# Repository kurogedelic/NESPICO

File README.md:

# NESPICO

A low-cost USB Famicom cartridge reader and **live-cartridge console** experiment.

The cartridge is not just a source for a ROM dump: the eventual console should drive the inserted physical cartridge's CPU and PPU buses while running the NES CPU/PPU/APU on an RP2350. The host PC or Mac handles display, audio playback, and controls.

## Project overview

```text
Physical Famicom 60-pin cartridge
               |
     74-series bus interface
     (latches / transceivers)
               |
      Raspberry Pi Pico 2 + PIO
               |
           USB Full Speed
               |
           PC / Mac host
   video, audio, controls, dumps
```

**Target hardware:** standard non-wireless Raspberry Pi Pico 2 (RP2350), 74-series logic, a real 60-pin cartridge connector and USB. The Pico 2 exposes 26 header GPIOs (GP0–GP22, GP26–GP28). For this design, GP26–GP28 are reserved for ADC0–ADC2 analog inputs; GP29 is ADC3 used by the board's VSYS monitor and is not a header GPIO. This leaves **23 digital GPIOs (GP0–GP22)**, so the earlier 27-GPIO concept must move at least four functions into external logic or be redesigned. No FPGA, HDMI shield or wireless module is planned. GPIO allocation and electrical protection are not finalized; see the [board architecture proposal](hardware/kicad/board-plan.md).

## Goals

1. **Play real cartridges.** Read PRG and CHR from the inserted cartridge during execution, support cartridge-side bank switching, CHR-RAM and mapper-generated IRQs instead of silently substituting a fully dumped ROM.
2. **Dump cartridges.** Read PRG-ROM and CHR-ROM to a host computer over USB, verify dumps, and support applicable mapper-controlled banks and cartridge save RAM.
3. **Reproduce physical-console behavior.** Keep motherboard RAM across RESET and cartridge replacement with power retained. Test tricks such as **Tennis → Super Mario Bros. World 9**. This is **not** a request for automatic hot-swap detection or live game switching; cartridge removal with power applied also needs electrical safety validation.
4. **Use the computer as the display.** Stream enough video/audio information over USB for a small PC/Mac viewer, and receive controller input from the host. USB Full Speed means raw full-frame 60fps video is not a feasible default protocol.
5. **Keep the hardware inexpensive and buildable in a quantity of two.** Prefer off-the-shelf Pico 2 boards, inexpensive standard logic and hand-assembled connectors to a custom MCU/FPGA board.

## Development approach

**Simulation first, hardware second.** The host-side simulator models approximate NTSC CPU/PPU bus demand, nominal 74-series/PIO transaction latency, overlapping requests, simplified MMC3 A12 qualification, RESET RAM retention and USB bandwidth assumptions. GitHub Actions runs the tests without any connected hardware.

The simulation is a *screening tool*, not proof that physical timing works. It does not execute actual PIO, emulate a complete 6502/PPU, validate the cartridge voltage interface, or establish real USB throughput. PPU events use classified 2-dot fetch slots from the documented rendering schedule, but do not include generated PPU addresses or rendering-state changes.

### Current status

- Host-side deterministic bus-timing simulator and 39 regression tests are present, including exhaustive five-step checks of the abstract shared-bus guard and PPU fetch-slot phase checks. The local suite and Pico SDK 2.3.1 firmware builds pass; invalid test GPIO maps are rejected before compilation. Both GitHub Actions workflows passed for commit `8f26041` on `work/rp2350-pio-bringup`.
- Firmware CI checks PIO instruction order, sample strobe side-set, loop width, and agreement between the calculated 99 instruction clocks and C constants. It builds a second test map using Pico 2 header GPIOs GP20–GP22 and GP26–GP28, and rejects duplicate, malformed, out-of-range, leading-zero, and board-reserved GPIO assignments. These are source/configuration checks, not hardware execution.
- A one-bit AHCT/LVC level-interface candidate schematic and a 35-case switch-level SPICE screen are now available under `hardware/`; the assumed cartridge release timing is not measured, so this is not electrical sign-off.
- GPIO pin map, 5V interface, physical timing, accurate NES emulator, cartridge swapping and USB video protocol remain to be validated.
- **No claim of working cartridge playback or real-device ROM dumping yet.**

### Local checks

```sh
python -m unittest discover -s tests -v
python -m nespico.cli --scanlines 262
python -m nespico.cli --sys-mhz 20 --settle-ns 160 --scanlines 1 # expected failure
python3 firmware/pio_bringup/validate_pio_source.py
```

## Development records

- [Development log (2026-10-12)](docs/journal/2026-10-12.md)
- [Development roadmap](docs/roadmap.md)
- [Simulation results](docs/benchmark-results.md)
- [PIO bring-up checkpoint](docs/pio-bringup.md)
- [Preliminary one-bit KiCad interface slice](hardware/kicad/README.md) and [Pico 2 board architecture proposal](hardware/kicad/board-plan.md)
- [Bus-turnaround SPICE screening model](hardware/spice/README.md)

## Milestones

1. CI timing simulator + executable design assumptions
2. PIO bus-pattern generator on Pico 2, measured with loopback and a logic analyzer
3. 74-series interface prototype: safe NROM PRG/CHR readback
4. USB dumper with validation and mapper-aware read/write
5. Real-cart CPU+PPU operation, host video/audio and input
6. RAM-preserving RESET, cartridge replacement tests and MMC1/MMC3

See [architecture notes](docs/architecture.md) and [simulation results](docs/benchmark-results.md). The extra pipeline tests model the CPU/PPU work required to prepare addresses; they show that nominal bus-only timing success is not sufficient.

The first Pico SDK / PIO firmware target is a **test-only dual-lane GPIO loopback** under `firmware/pio_bringup/`. It is intentionally not a cartridge bus driver; see its [build and safety instructions](firmware/pio_bringup/README.md). A board-specific pinout and real logic-analyzer measurements are still required before freezing a cartridge interface or releasing PCB files for fabrication.

Reference documentation: [NESdev cartridge connector](https://www.nesdev.org/wiki/Cartridge_connector), [PPU rendering](https://www.nesdev.org/wiki/PPU_rendering), [MMC3](https://www.nesdev.org/wiki/MMC3), [RP2350](https://www.raspberrypi.com/documentation/microcontrollers/silicon.html).

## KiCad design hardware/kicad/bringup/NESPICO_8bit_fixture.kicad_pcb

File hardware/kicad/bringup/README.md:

# NESPICO Pico 2 8-bit bring-up fixture (draft)

This is a **bench-test fixture**, not the full Famicom cartridge interface and **not a fabrication release**. It exercises two independent 8-bit paths around a standard, non-wireless Raspberry Pi Pico 2:

- **CPU TX:** Pico GP0–GP7 → SN74AHCT245 (A→B, 5 V side) → J3 test header.
- **PPU RX:** J4 5 V-tolerant test header → SN74LVC245A (B→A) → Pico GP8–GP15.
- **Controls:** GP16 drives TX_OE_N; GP17 drives RX_OE_N. Separate 10 kΩ pull-ups keep both active-low enables disabled while the Pico is high impedance.
- **ADC breakout:** GP26–GP28 are analog-only. GP29 is not routed; the Pico 2 uses it internally for VSYS/3 measurement.
- **Power boundary:** USB VBUS powers only the AHCT test buffer. No cartridge power rail or cartridge connector is present. J3/J4 are labelled test-only.

The current rectangular outline is 100 × 82 mm, with two copper layers. The Pico 2 socket rows are 17.78 mm apart and span 48.26 mm. J1/J2 are standard 1×20 socket-strip footprints; confirm the actual socket height and module fit before assembly.

## Pico 2 physical-pin mapping

The local 1×20 connector pad number follows the footprint from top to bottom. With the Pico USB connector at the top, the left side is physical pins 1→20 (`J1`), while the right side is physical pins 40→21 (`J2`). This orientation is checked against Figure 4 of the [Raspberry Pi Pico 2 datasheet](https://pip.raspberrypi.com/documents/RP-008299-DS).

| PCB connector/pad | Pico 2 physical pin | Pico signal | Fixture net / destination |
| --- | ---: | --- | --- |
| J2.1 | 40 | VBUS | +5V_USB, U1 only |
| J2.5 | 36 | 3V3 | +3V3 logic rail |
| J2.7 | 34 | GP28 / ADC2 | J5.1, ADC2_IN |
| J2.8 | 33 | AGND | J5.2, AGND |
| J2.9 | 32 | GP27 / ADC1 | J5.3, ADC1_IN |
| J2.10 | 31 | GP26 / ADC0 | J5.4, ADC0_IN |
| J2.19 | 22 | GP17 | RX_OE_N |
| J2.20 | 21 | GP16 | TX_OE_N |

**J5 order:** `1 ADC2`, `2 AGND`, `3 ADC1`, `4 ADC0`. Keep GP26–GP28 exclusively for analog use in this pin-allocation baseline. **Never drive J5 above 3.3 V or while the Pico is unpowered.** There is no input divider, series protection, or source-conditioning network because the analog source has not been defined; only connect a reviewed 0–3.3 V source with suitable impedance. GP29/ADC3 is internal to the Pico 2 and is not broken out.

## Candidate parts (not a qualified production BOM)

| Reference | Candidate | Footprint | Notes |
| --- | --- | --- | --- |
| U1 | SN74AHCT245DW | SOIC-20W | 5 V supply; fixed A→B; 3.3 V GPIO input meets AHCT VIH under datasheet conditions |
| U2 | SN74LVC245ADW | SOIC-20W | 3.3 V supply; fixed B→A; 5 V-tolerant input under datasheet conditions |
| R1, R2 | 10 kΩ, 0805 | 0805 metric | OE pull-ups; placeholder values |
| C1, C2 | 100 nF, 0805 | 0805 metric | Local bypass placeholders; final placement/value review required |
| J1, J2 | 1×20 female socket strips, 2.54 mm | KiCad standard THT | Check mating height and module fit |
| J3, J4 | 1×10 male pin headers, 2.54 mm | KiCad standard THT | Test-only; not a cartridge connection |
| J5 | 1×4 male pin header, 2.54 mm | KiCad standard THT | ADC-only, 0–3.3 V maximum |

Check the exact orderable component, package suffix, supply/logic limits, bypass layout, and assembly fit against complete datasheets before ordering. The component values are candidates, not a recommendation for a final interface.

## Files and regeneration

- `NESPICO_8bit_fixture.kicad_pro` — KiCad project.
- `NESPICO_8bit_fixture.kicad_sch` — editable schematic.
- `NESPICO_8bit_fixture.kicad_pcb` — editable two-layer PCB.
- `generate_bringup.py` — regenerates the schematic and board using the installed KiCad symbol/footprint libraries.
- `validate_bringup.py` — checks the schematic/PCB pin-net agreement, physical Pico header numbering, ADC reservation, 5 V boundary, and KiCad connectivity.
- `validate_clearance.py` — optional shape-aware, layer-aware 0.20 mm copper spacing screen; requires Shapely in the same Python environment as `pcbnew`.
- `BOM_draft.csv` — unqualified candidate bill of materials; generic connector/passive MPNs remain unselected.
- `references.md` — primary-source device and mechanical references.
- `previews/` — PDF schematic and front/back PCB previews plus SVG layer previews.
- `gerber-draft/` and `NESPICO_8bit_fixture_fab_draft.zip` — provisional Gerber/Excellon outputs for review only.

From the repository root:

```sh
/usr/bin/python3 hardware/kicad/bringup/generate_bringup.py
/usr/bin/python3 hardware/kicad/bringup/validate_bringup.py
# Optional; requires Shapely in the pcbnew Python environment.
/usr/bin/python3 hardware/kicad/bringup/validate_clearance.py
```

The schematic/PCB pin-net validator passes with zero unconnected connections. The optional shape-aware screen checks 130 track/via objects and 112 pads (22,322 relevant pairs) using copper-layer intersections and the actual circle/oval pad shapes; the current result is zero different-net violations below 0.20 mm. The installed KiCad 7 CLI exposes PCB export but not a PCB DRC subcommand; **run the native KiCad DRC and review fabrication outputs on the final candidate before any board order**. Confirm socket/module/mechanical fit and actual electrical behavior on the bench.

## Not included / no release implied

There is no 60-pin cartridge connector, address-latch bank, CIRAM/audio/IRQ logic, cartridge power switching, current limit, reverse-current protection, connector-side ESD network, hot-plug sequence, or final GPIO schedule. The earlier 27-function concept still exceeds the 23 digital external-header GPIOs available when GP26–GP28 are kept for ADC and GP29 remains internal. Those architecture and electrical-safety gates must be resolved before designing or releasing a full cartridge PCB.

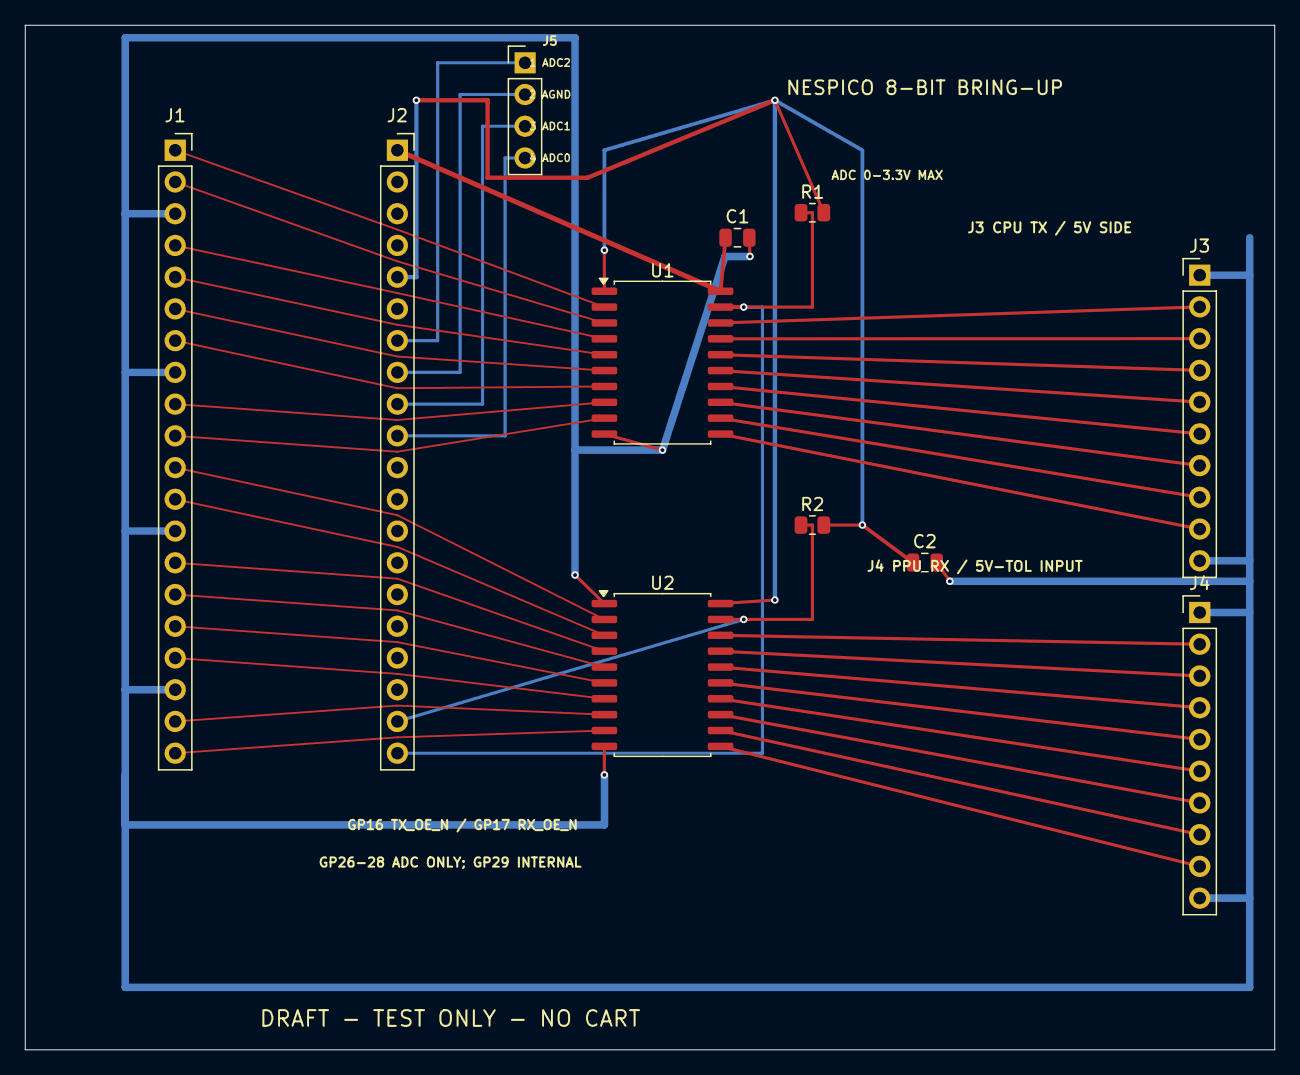
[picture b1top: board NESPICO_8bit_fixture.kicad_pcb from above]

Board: 2 copper layers, 100.0 x 82.0 mm, 11 parts (0 on the bottom side), 41 nets.

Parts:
C1: 100n U1 bypass; C_0805_2012Metric
C2: 100n U2 bypass; C_0805_2012Metric
J1: Pico 2 left socket; PinSocket_1x20_P2.54mm_Vertical
J2: Pico 2 right socket; PinSocket_1x20_P2.54mm_Vertical
J3: CPU TX TEST ONLY - 5V SIDE; PinHeader_1x10_P2.54mm_Vertical
J4: PPU RX TEST INPUT - 5V TOLERANT; PinHeader_1x10_P2.54mm_Vertical
J5: ADC ONLY 0-3V3; PinHeader_1x04_P2.54mm_Vertical
R1: 10k TX_OE_N pull-up; R_0805_2012Metric
R2: 10k RX_OE_N pull-up; R_0805_2012Metric
U1: SN74AHCT245DW CPU TX; SOIC-20W_7.5x12.8mm_P1.27mm
U2: SN74LVC245ADW PPU RX; SOIC-20W_7.5x12.8mm_P1.27mm

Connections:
+3V3: C2.1, J2.5, R1.2, R2.2, U1.1, U2.20
+5V_USB: C1.1, J2.1, U1.20
ADC0_IN: J2.10, J5.4
ADC1_IN: J2.9, J5.3
ADC2_IN: J2.7, J5.1
AGND: J2.8, J5.2
CPU_D0: J1.1, U1.2
CPU_D1: J1.2, U1.3
CPU_D2: J1.4, U1.4
CPU_D3: J1.5, U1.5
CPU_D4: J1.6, U1.6
CPU_D5: J1.7, U1.7
CPU_D6: J1.9, U1.8
CPU_D7: J1.10, U1.9
GND: C1.2, C2.2, J1.3, J1.8, J1.13, J1.18, J3.1, J3.10, J4.1, J4.10, U1.10, U2.1, U2.10
PPU_D0: J1.11, U2.2
PPU_D1: J1.12, U2.3
PPU_D2: J1.14, U2.4
PPU_D3: J1.15, U2.5
PPU_D4: J1.16, U2.6
PPU_D5: J1.17, U2.7
PPU_D6: J1.19, U2.8
PPU_D7: J1.20, U2.9
RX_OE_N: J2.19, R2.1, U2.19
RX_TEST_D0: J4.2, U2.18
RX_TEST_D1: J4.3, U2.17
RX_TEST_D2: J4.4, U2.16
RX_TEST_D3: J4.5, U2.15
RX_TEST_D4: J4.6, U2.14
RX_TEST_D5: J4.7, U2.13
RX_TEST_D6: J4.8, U2.12
RX_TEST_D7: J4.9, U2.11
TX_OE_N: J2.20, R1.1, U1.19
TX_TEST_D0: J3.2, U1.18
TX_TEST_D1: J3.3, U1.17
TX_TEST_D2: J3.4, U1.16
TX_TEST_D3: J3.5, U1.15
TX_TEST_D4: J3.6, U1.14
TX_TEST_D5: J3.7, U1.13
TX_TEST_D6: J3.8, U1.12
TX_TEST_D7: J3.9, U1.11

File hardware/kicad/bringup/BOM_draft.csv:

Reference,Qty,Candidate value / part,Footprint,Manufacturer / MPN,Notes
U1,1,SN74AHCT245DW,SOIC-20W 7.5x12.8 mm P1.27,Texas Instruments / SN74AHCT245DW,Fixed A-to-B 5 V transmit test path; verify exact package and datasheet
U2,1,SN74LVC245ADW,SOIC-20W 7.5x12.8 mm P1.27,Texas Instruments / SN74LVC245ADW,Fixed B-to-A 3.3 V receive path; verify 5 V input conditions
R1 R2,2,10 kOhm 1 percent 0805,0805 metric,Generic / not selected,OE_N pull-ups; placeholder value
C1 C2,2,100 nF X7R 25 V 0805,0805 metric,Generic / not selected,Local bypass placeholders; confirm final value/placement
J1 J2,2,1x20 female socket strip 2.54 mm,PinSocket_1x20_P2.54mm_Vertical,Generic / not selected,Check stack height and Pico 2 fit
J3 J4,2,1x10 male pin header 2.54 mm,PinHeader_1x10_P2.54mm_Vertical,Generic / not selected,Test-only headers; not cartridge connectors
J5,1,1x4 male pin header 2.54 mm,PinHeader_1x04_P2.54mm_Vertical,Generic / not selected,ADC2 AGND ADC1 ADC0; 0-3.3 V maximum
